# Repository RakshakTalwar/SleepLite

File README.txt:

This is an open collection of files for the SleepLite to allow the SleepLite to be fully open source and in public domain. 

You are free to use this any way you choose, non-commercial, commercial, or hobby use. 
Please give due credit. 

You can also purchase a kit with all the components, PCB, and preflashed microcontroller
here --> http://www.jameco.com/webapp/wcs/stores/servlet/ProductDisplay?search_type=jamecoall&catalogId=10001&freeText=sleeplite&langId=-1&productId=2184157&storeId=10001&ddkey=http:StoreCatalogDrillDownView

Full tutorial with pictures, code, etc. is available 
here --> http://raptorbird.com/sleeplite-kit.php

I invested time and resources into making SleepLite fully open source and accessible, please support me by buying from Jameco or by contacting me for one directly at contact@raptorbird.com.

Written by Rakshak Talwar of RaptorBird.
Fully open source, hack your way to better sleep!

The software, information about hardware, hardware, and any other information here is without warranty. It is your responsibility only. 
This device has not been evaluated by the Food and Drug Administration and is not intended to diagnose, treat, cure or prevent any disease.
Caution: Do not use if you have heart problems or are prone to epileptic seizures.

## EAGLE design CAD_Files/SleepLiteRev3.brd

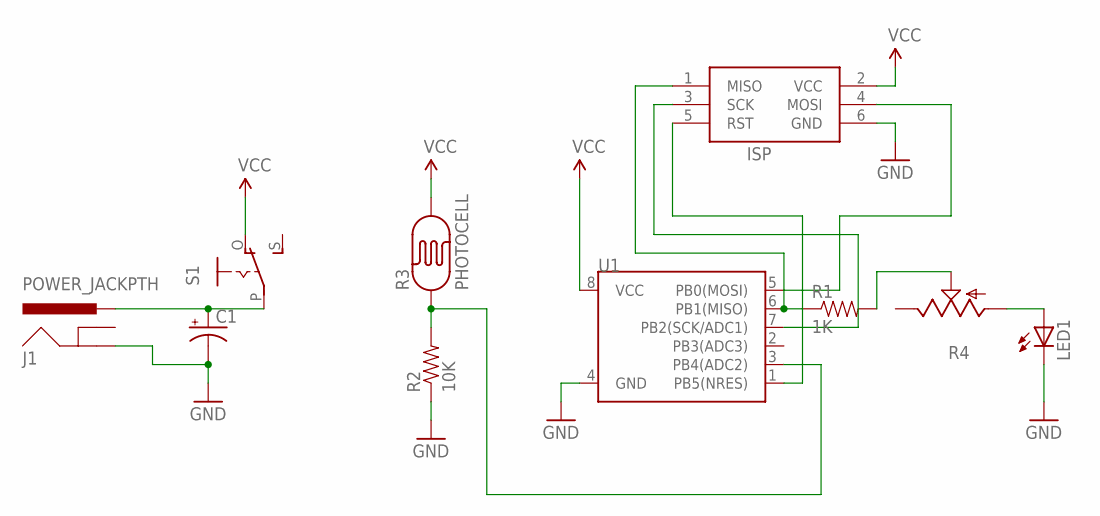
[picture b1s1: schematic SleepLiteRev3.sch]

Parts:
C1: CAP_POLPTH2; CPOL-RADIAL-10UF-25V
ISP: AVRISP-6; AVRISP
J1: POWER_JACKPTH; POWER_JACK_PTH
LED1: LED5MM
R1: 1K; AXIAL-0.4
R2: 10K; AXIAL-0.4
R3: PHOTOCELL; PHOTOCELL-KIT
R4: TRIM_US-B64Y; B64Y
S1: EG1218S; EG1218
U1: ATTINY13DIP; DIP08

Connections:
GND: C1.2 (-), ISP.6 (GND), J1.GND, LED1.K (C), R2.P$1 (1), U1.4 (GND)
unnamed: C1.1 (+), J1.PWR, S1.P
unnamed: R2.P$2 (2), R3.1, U1.3 (PB4(ADC2))
unnamed: ISP.1 (MISO), R1.P$1 (1), U1.6 (PB1(MISO))
unnamed: R1.P$2 (2), R4.S
unnamed: LED1.A, R4.A
unnamed: ISP.5 (RST), U1.1 (PB5(NRES))
unnamed: ISP.4 (MOSI), U1.5 (PB0(MOSI))
unnamed: ISP.3 (SCK), U1.7 (PB2(SCK/ADC1))
VCC: ISP.2 (VCC), R3.2, S1.O, U1.8 (VCC)

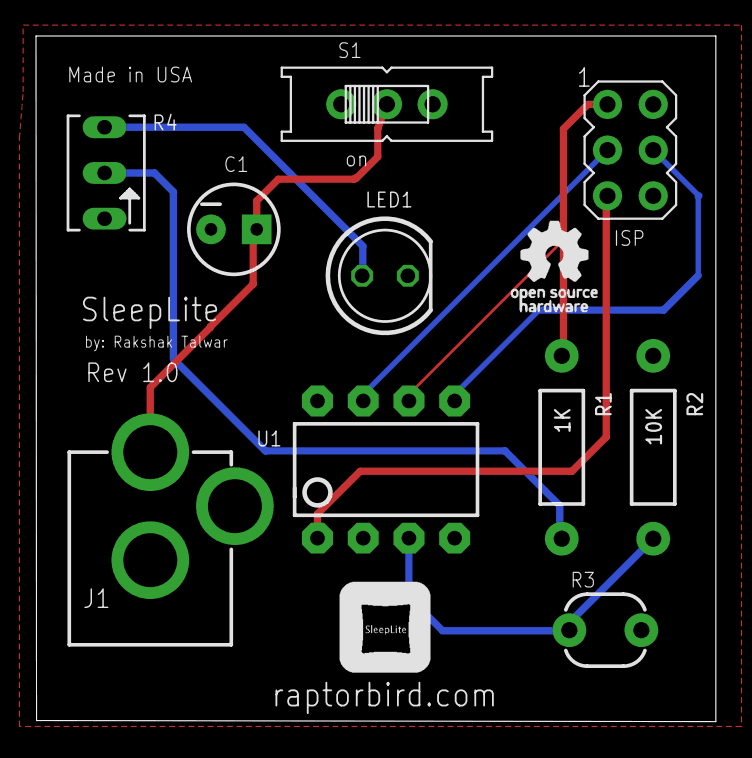
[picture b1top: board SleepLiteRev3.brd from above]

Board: 2 copper layers, 37.8 x 38.1 mm, 10 parts (0 on the bottom side), 10 nets.

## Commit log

2013-06-14 First Upload
    First upload of original files. Including instructions, CAD files,
    code, etc.
2013-12-24 Create LICENSE

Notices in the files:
parts and their libraries:
SparkFun-Connectors: Licensing: CC v3.0 Share-Alike You are welcome to use this library for commercial purposes.
